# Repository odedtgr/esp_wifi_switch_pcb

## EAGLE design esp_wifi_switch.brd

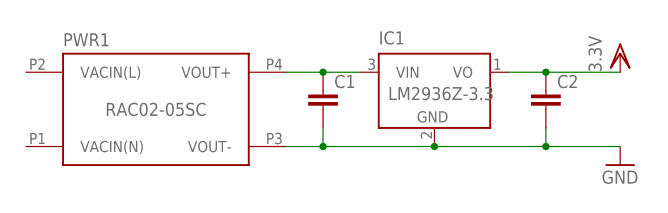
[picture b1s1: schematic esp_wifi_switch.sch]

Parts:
C1, C2: C-EU025-025X050; C025-025X050
IC1: LM2936Z-3.3; TO92
PWR1: RAC02-05SC; LOW_PROFILE_POWER_MODULE

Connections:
GND: C1.2, C2.2, IC1.2 (GND), PWR1.P3 (VOUT-)
unnamed: C1.1, IC1.3 (VIN), PWR1.P4 (VOUT+)
VACIN(L): PWR1.P2 (VACIN(L))
VACIN(N): PWR1.P1 (VACIN(N))
VDD: C2.1, IC1.1 (VO)

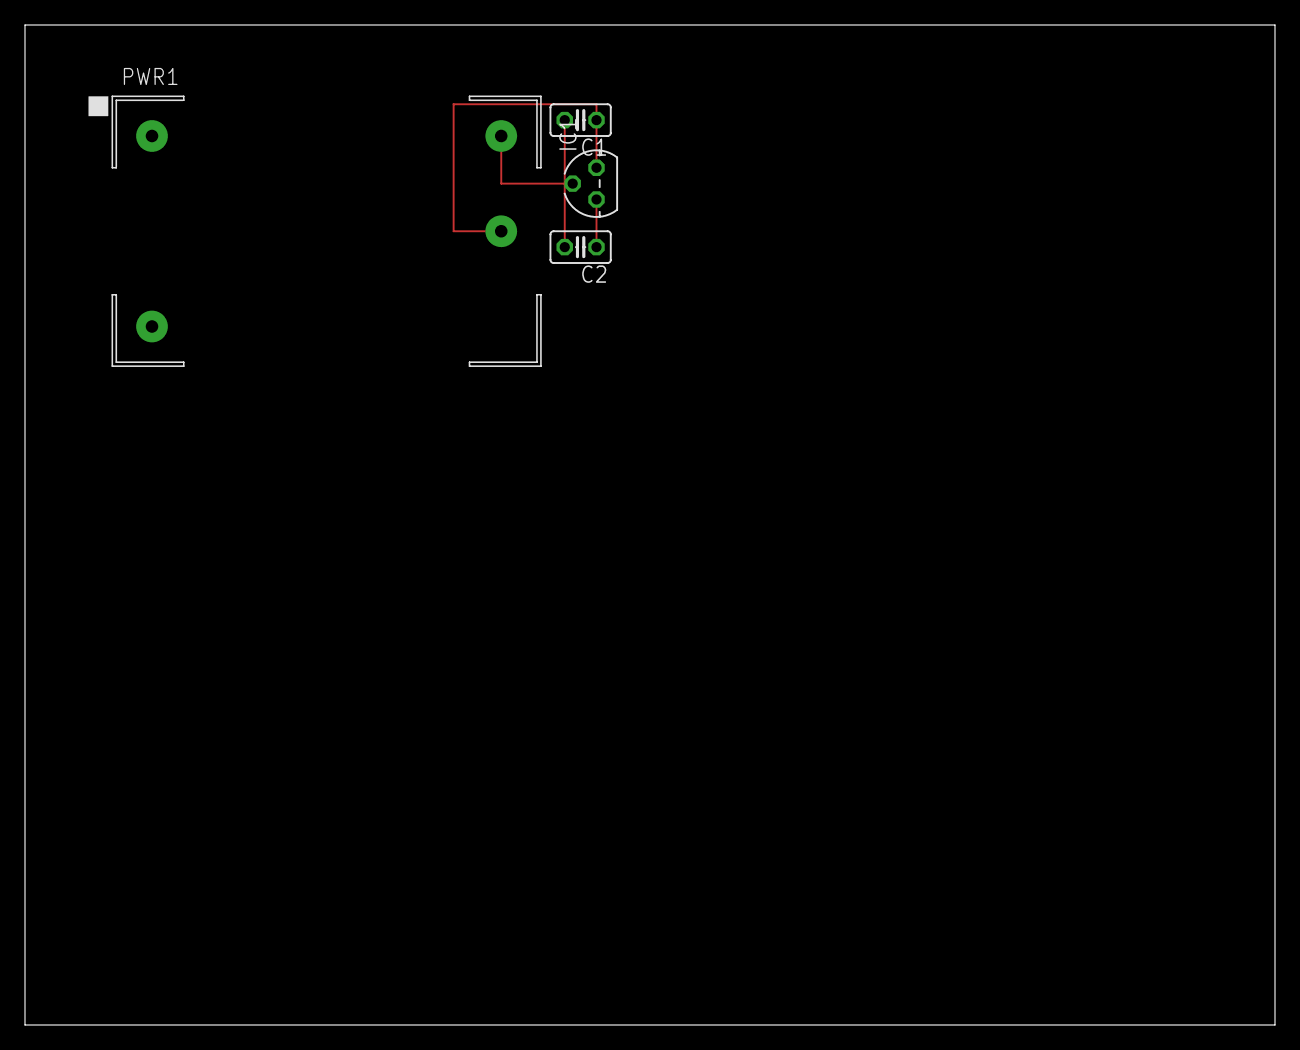
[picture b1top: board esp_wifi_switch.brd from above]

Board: 2 copper layers, 100.0 x 80.0 mm, 4 parts (0 on the bottom side), 3 nets.

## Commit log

2017-11-15 :neckbeard: Added .gitattributes & .gitignore files
2017-11-15 First commit - AC/DC
2017-11-29 backup commit
